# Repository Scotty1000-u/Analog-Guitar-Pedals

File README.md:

# Analog-Guitar-Pedals
Transcriptions of Notes/Designs for since starting to design guitar pedals. I just add my random finished pedals to this repo.

## Boost Pedal 
#### Schematics: 
Shows both the KiCad and LT Spice schematic design. The LT Spice has the probe for the imput and output waveform showing the boosted output.

***

#### KiCad PCB Mock up: 
Shows the mockup of the PCB and the routing. Uses 9V battery.

***

## Bazz Fuzz Pedal: Simple Pedal made off of the bazz fuzz typology.
#### Schematics: 
Shows both the KiCad and LT Spice schematic design. The LT Spice probs imput and output waveform showing the DC clipping at the output.

***

#### KiCad PCB Mock up: 
Shows the mockup of the PCB and the routing. Uses a 9V Barrel Jack.

***

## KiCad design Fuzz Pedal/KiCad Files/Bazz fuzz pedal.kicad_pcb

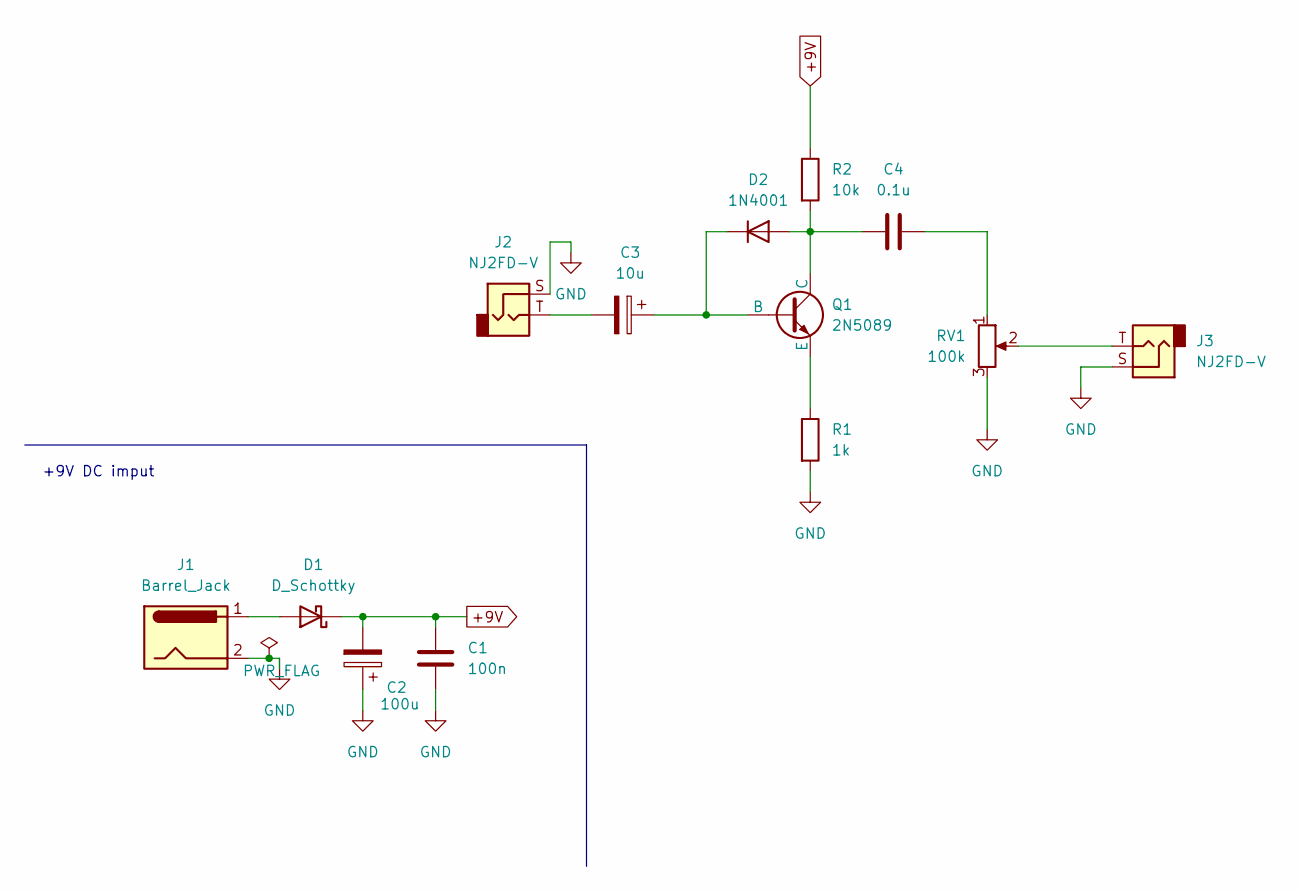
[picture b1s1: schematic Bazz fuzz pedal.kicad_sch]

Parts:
C1: 100n; C_Disc_D5.0mm_W2.5mm_P5.00mm
C2: 100u; CP_Radial_D6.3mm_P2.50mm
C3: 10u; CP_Radial_D5.0mm_P2.00mm
C4: 0.1u; CP_Radial_D5.0mm_P2.00mm
D1: D_Schottky; D_DO-41_SOD81_P10.16mm_Horizontal
D2: 1N4001; D_DO-41_SOD81_P10.16mm_Horizontal
J1: Barrel_Jack; BarrelJack_CUI_PJ-063AH_Horizontal
J2, J3: NJ2FD-V; Jack_6.35mm_Neutrik_NJ2FD-V_Vertical
Q1: 2N5089; TO-92
R1: 1k; R_Axial_DIN0207_L6.3mm_D2.5mm_P10.16mm_Horizontal
R2: 10k; R_Axial_DIN0207_L6.3mm_D2.5mm_P10.16mm_Horizontal
RV1: 100k; Potentiometer_ACP_CA6-VSMD_Vertical

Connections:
+9V: C1.1, C2.2, D1.1 (K), R2.1
GND: C1.2, C2.1, J1.2, J2.S, J3.S, R1.2, RV1.3
unnamed: C3.2, J2.T
unnamed: C4.2, RV1.1
unnamed: D1.2 (A), J1.1
unnamed: C4.1, D2.2 (A), Q1.1 (C), R2.2
unnamed: C3.1, D2.1 (K), Q1.2 (B)
unnamed: J3.T, RV1.2
unnamed: Q1.3 (E), R1.1

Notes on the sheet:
+9V DC imput

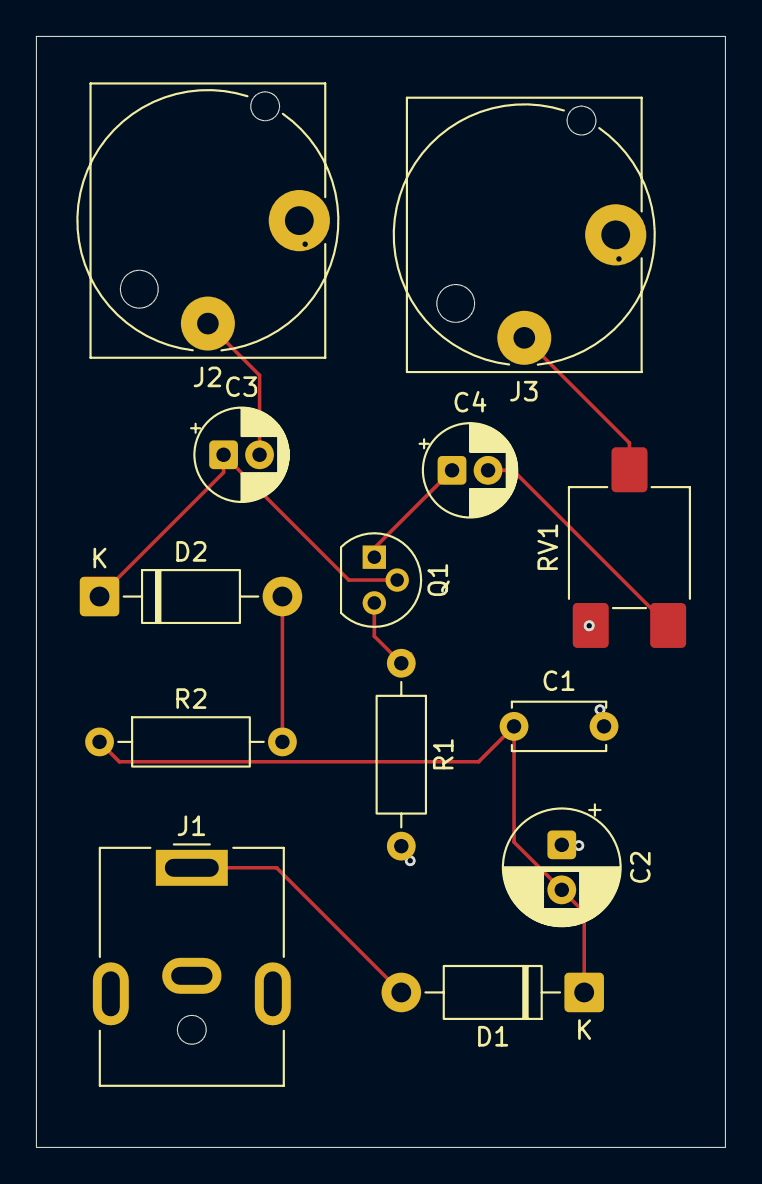
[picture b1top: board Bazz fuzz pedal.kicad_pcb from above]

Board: 2 copper layers, 38.3 x 61.7 mm, 13 parts (0 on the bottom side), 9 nets.

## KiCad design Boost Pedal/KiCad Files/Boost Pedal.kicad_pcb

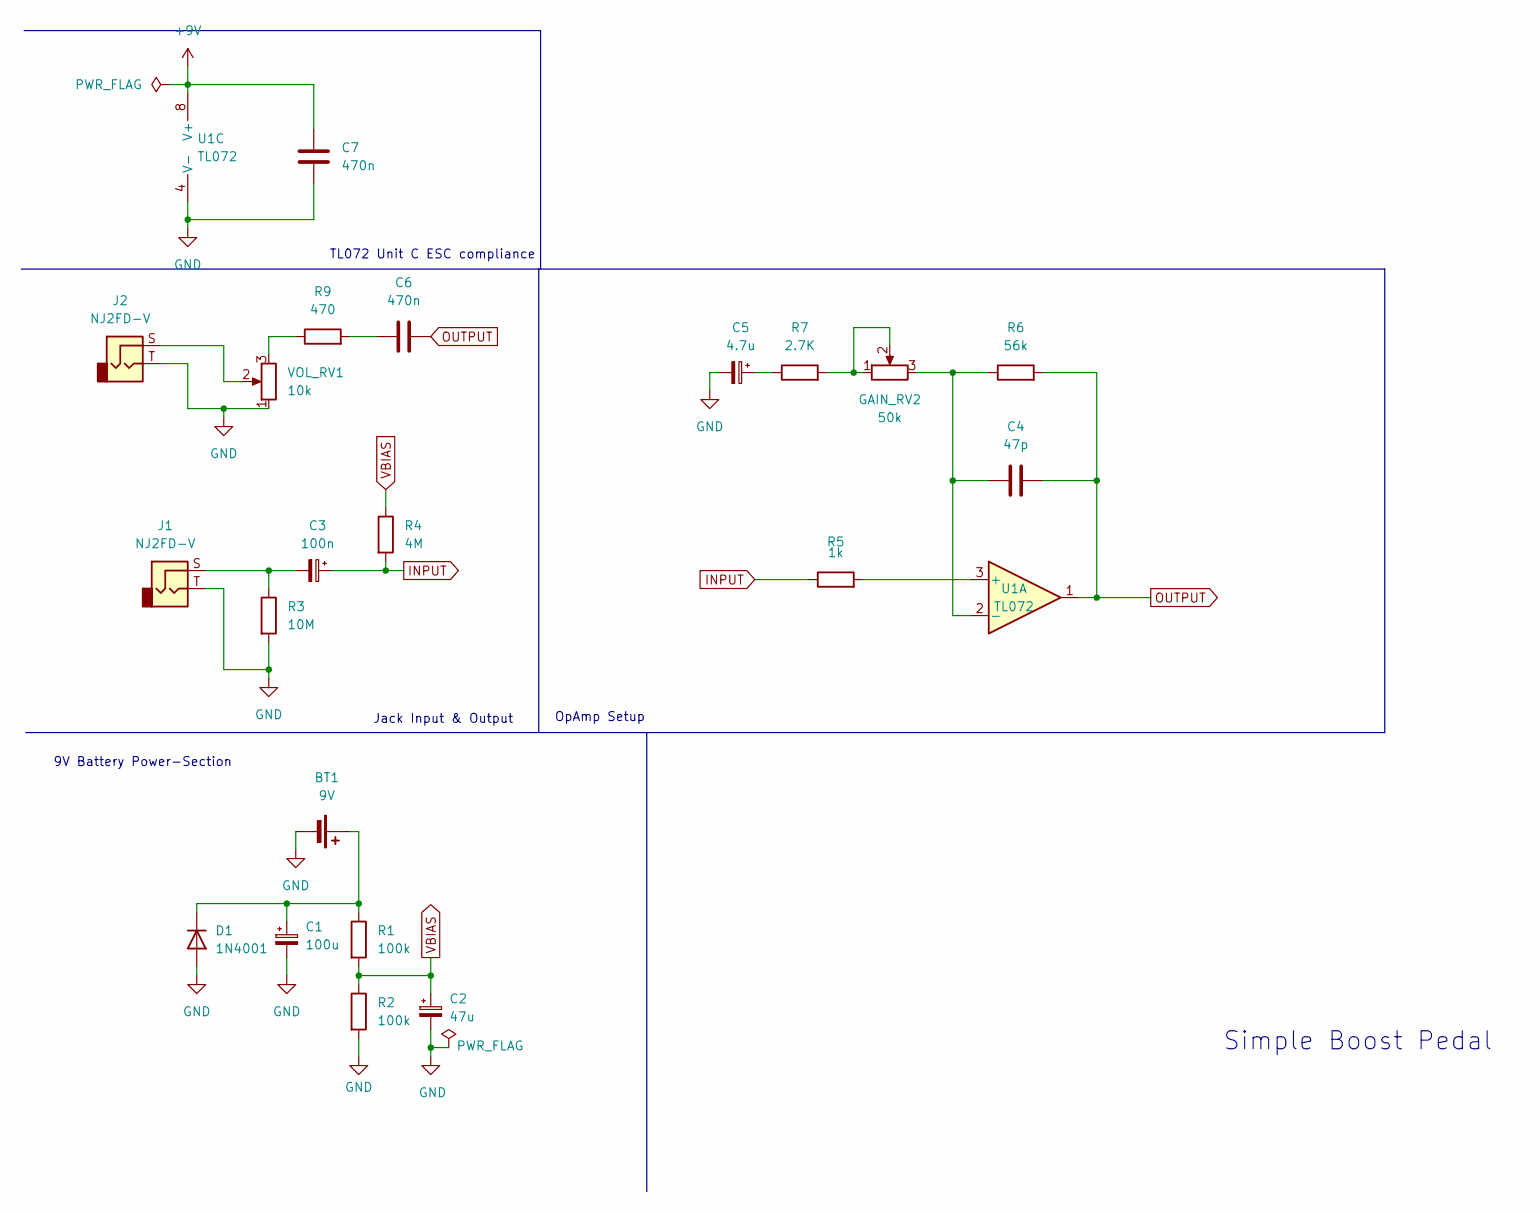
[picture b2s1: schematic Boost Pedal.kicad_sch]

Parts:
BT1: 9V; JST_XH_B2B-XH-A_1x02_P2.50mm_Vertical
C1: 100u; CP_Elec_8x10
C2: 47u; CP_Elec_8x10
C3: 100n; CP_Elec_8x10
C4: 47p; C_0805_2012Metric
C5: 4.7u; CP_Elec_8x10
C6: 470n; C_1206_3216Metric
C7: 470n
D1: 1N4001; D_DO-41_SOD81_P10.16mm_Horizontal
GAIN_RV2: 50k; Potentiometer_Alpha_RD901F-40-00D_Single_Vertical
J1, J2: NJ2FD-V; Jack_6.35mm_Neutrik_NJ2FD-V_Vertical
R1, R2: 100k; R_0805_2012Metric
R3: 10M; R_0805_2012Metric
R4: 4M; R_0805_2012Metric
R5: 1k; R_0805_2012Metric
R6: 56k; R_0805_2012Metric
R7: 2.7K; R_0805_2012Metric
R9: 470; R_0805_2012Metric
U1: TL072; SOIC-8_3.9x4.9mm_P1.27mm
VOL_RV1: 10k; Potentiometer_Alpha_RD901F-40-00D_Single_Vertical

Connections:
+9V: C7.2, U1.8 (V+)
GND: BT1.2 (-), C1.2, C2.2, C5.2, C7.1, D1.2 (A), J1.T, J2.T, R2.2, R3.2, U1.4 (V-), VOL_RV1.1
INPUT: C3.1, R4.2, R5.1
unnamed: BT1.1 (+), C1.1, D1.1 (K), R1.1
unnamed: C3.2, J1.S, R3.1
unnamed: C5.1, R7.1
unnamed: C6.1, R9.2
unnamed: GAIN_RV2.1, GAIN_RV2.2, R7.2
unnamed: J2.S, VOL_RV1.2
unnamed: R9.1, VOL_RV1.3
unnamed: R5.2, U1.3 (+)
unnamed: C4.1, GAIN_RV2.3, R6.1, U1.2 (-)
OUTPUT: C4.2, C6.2, R6.2, U1.1
VBIAS: C2.1, R1.2, R2.1, R4.1

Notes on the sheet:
9V Battery Power-Section
OpAmp Setup
Jack Input & Output
TL072 Unit C ESC compliance
Simple Boost Pedal

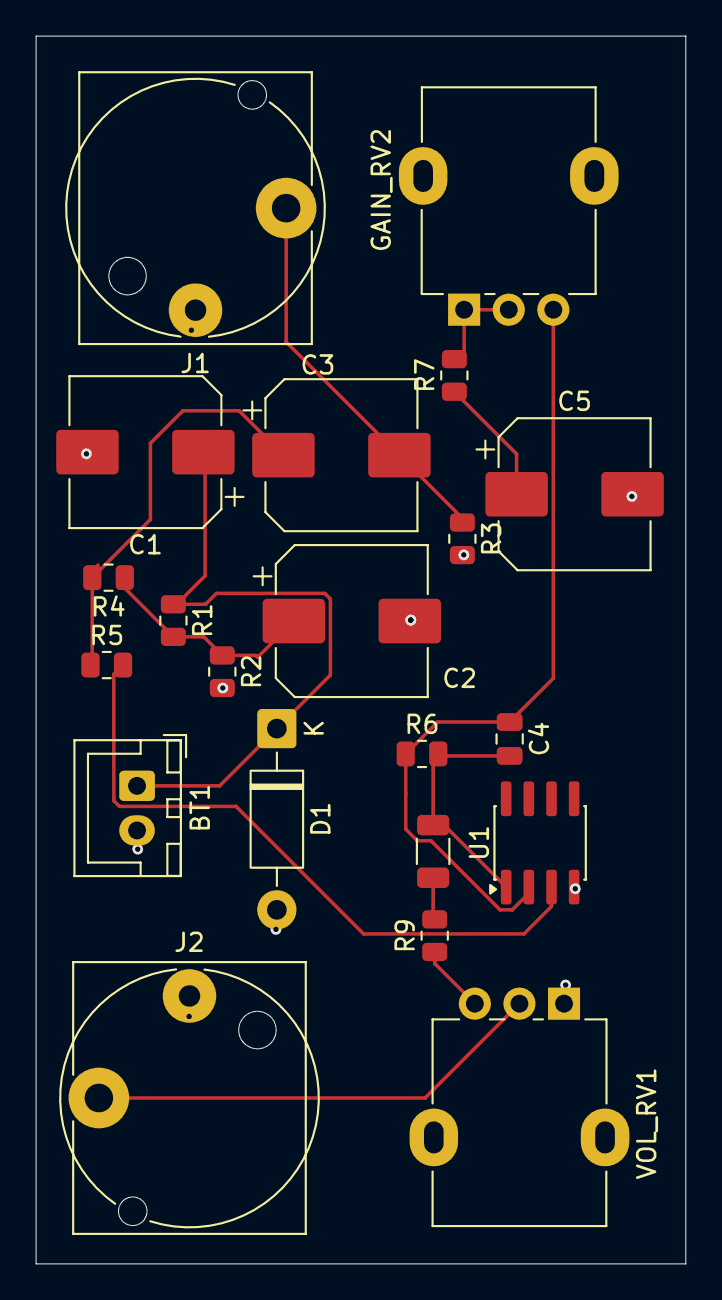
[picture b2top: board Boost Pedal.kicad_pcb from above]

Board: 2 copper layers, 36.4 x 68.8 mm, 21 parts (0 on the bottom side), 13 nets.
